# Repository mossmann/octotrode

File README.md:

# octotrode
optical replacement switches for Wico 8-way joystick

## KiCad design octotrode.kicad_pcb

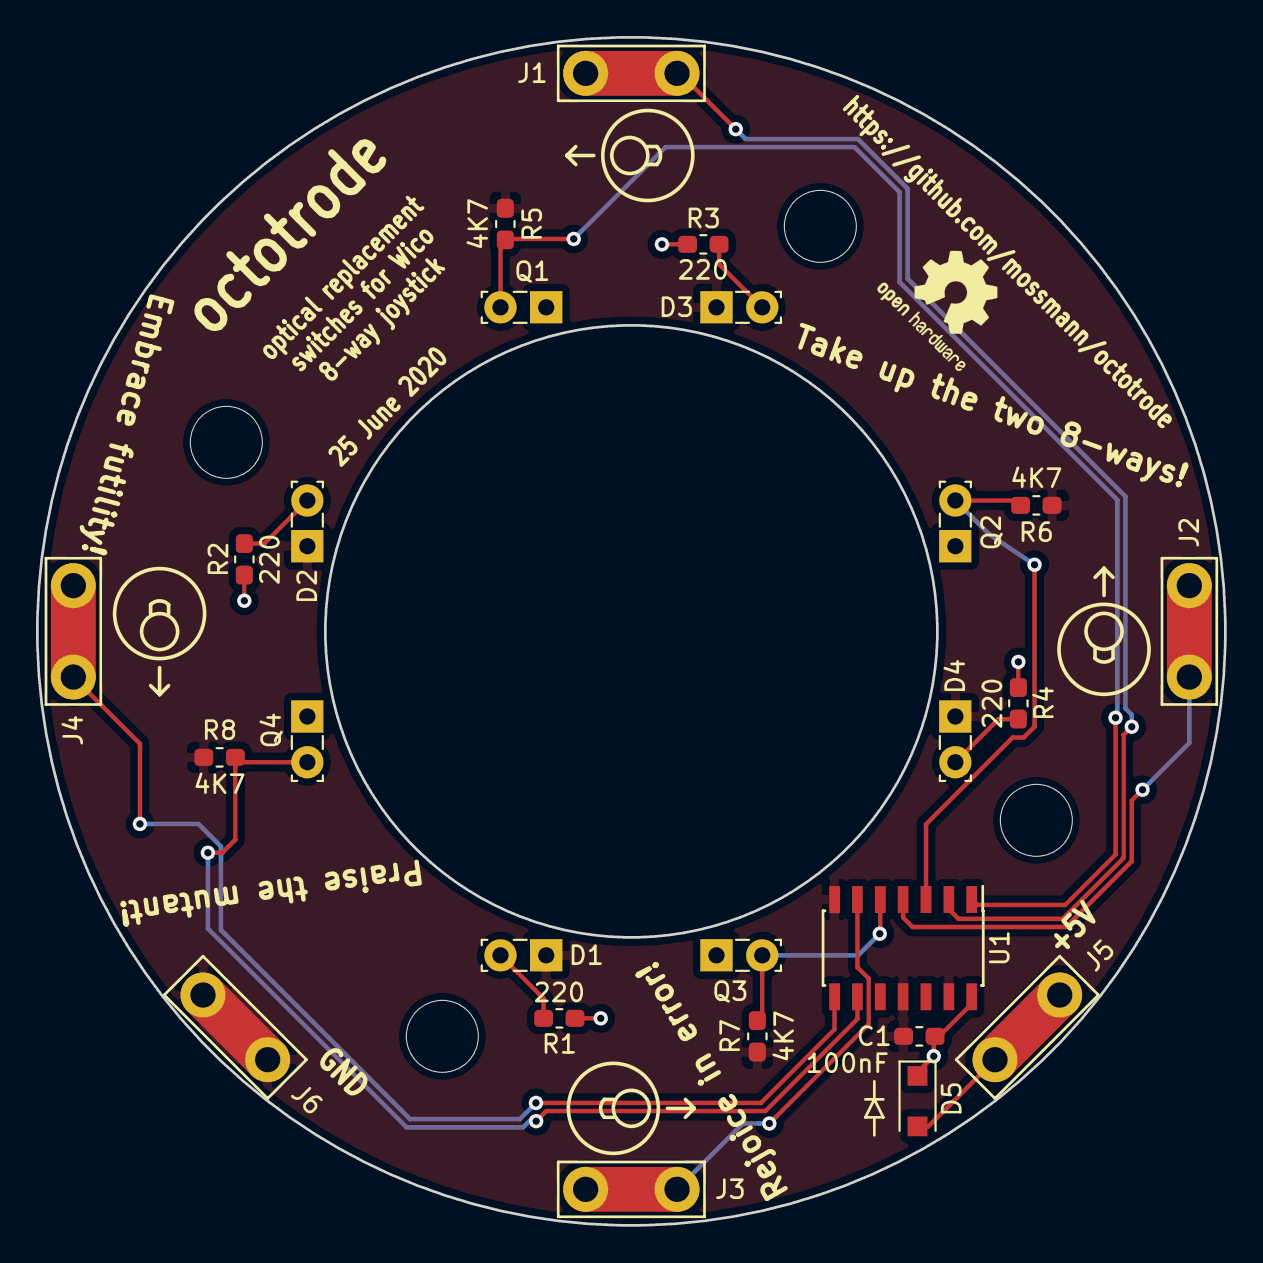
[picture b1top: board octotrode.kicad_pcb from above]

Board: 2 copper layers, 66.0 x 66.0 mm, 25 parts (0 on the bottom side), 15 nets.

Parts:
C1: 100nF; C_0603_1608Metric_Pad1.05x0.95mm_HandSolder
D1, D2, D3, D4: LED; LED_SideEmitter_Rectangular_W4.5mm_H1.6mm
D5: D; D_SOD-123F
J1, J2, J3, J4, J5, J6: Conn_01x01; Conn_QC_Tab_0.25in
Q1, Q2, Q3, Q4: Q_Photo_NPN; LED_SideEmitter_Rectangular_W4.5mm_H1.6mm
R1, R2, R3, R4: 220; R_0603_1608Metric_Pad1.05x0.95mm_HandSolder
R5, R6, R7, R8: 4K7; R_0603_1608Metric_Pad1.05x0.95mm_HandSolder
U1: 74HC14; SOIC-14_3.9x8.7mm_P1.27mm

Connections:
+5V: C1.1, D5.1, Q1.1, Q2.1, Q3.1, Q4.1, R1.1, R2.1, R3.1, R4.1, U1.14
GND: C1.2, D1.1, D2.1, D3.1, D4.1, J6.1, R5.2, R6.2, R7.2, R8.2, U1.7, U1.11, U1.13
unnamed: D1.2, R1.2
unnamed: D2.2, R2.2
unnamed: D3.2, R3.2
unnamed: D4.2, R4.2
unnamed: D5.2, J5.1
unnamed: J1.1, U1.2
unnamed: J2.1, U1.4
unnamed: J3.1, U1.6
unnamed: J4.1, U1.8
unnamed: Q1.2, R5.1, U1.1
unnamed: Q2.2, R6.1, U1.3
unnamed: Q3.2, R7.1, U1.5
unnamed: Q4.2, R8.1, U1.9

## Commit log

2019-07-14 complete design
2020-06-25 add reverse voltage protection
2020-06-25 correct LED orientation
2020-06-25 widen optics position, shrink board
2020-06-25 update license and bill of materials

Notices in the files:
octotrode.kicad_pcb:
Copyright 2019-2020 Michael Ossmann
Licensed under the CERN-OHL-P v2
